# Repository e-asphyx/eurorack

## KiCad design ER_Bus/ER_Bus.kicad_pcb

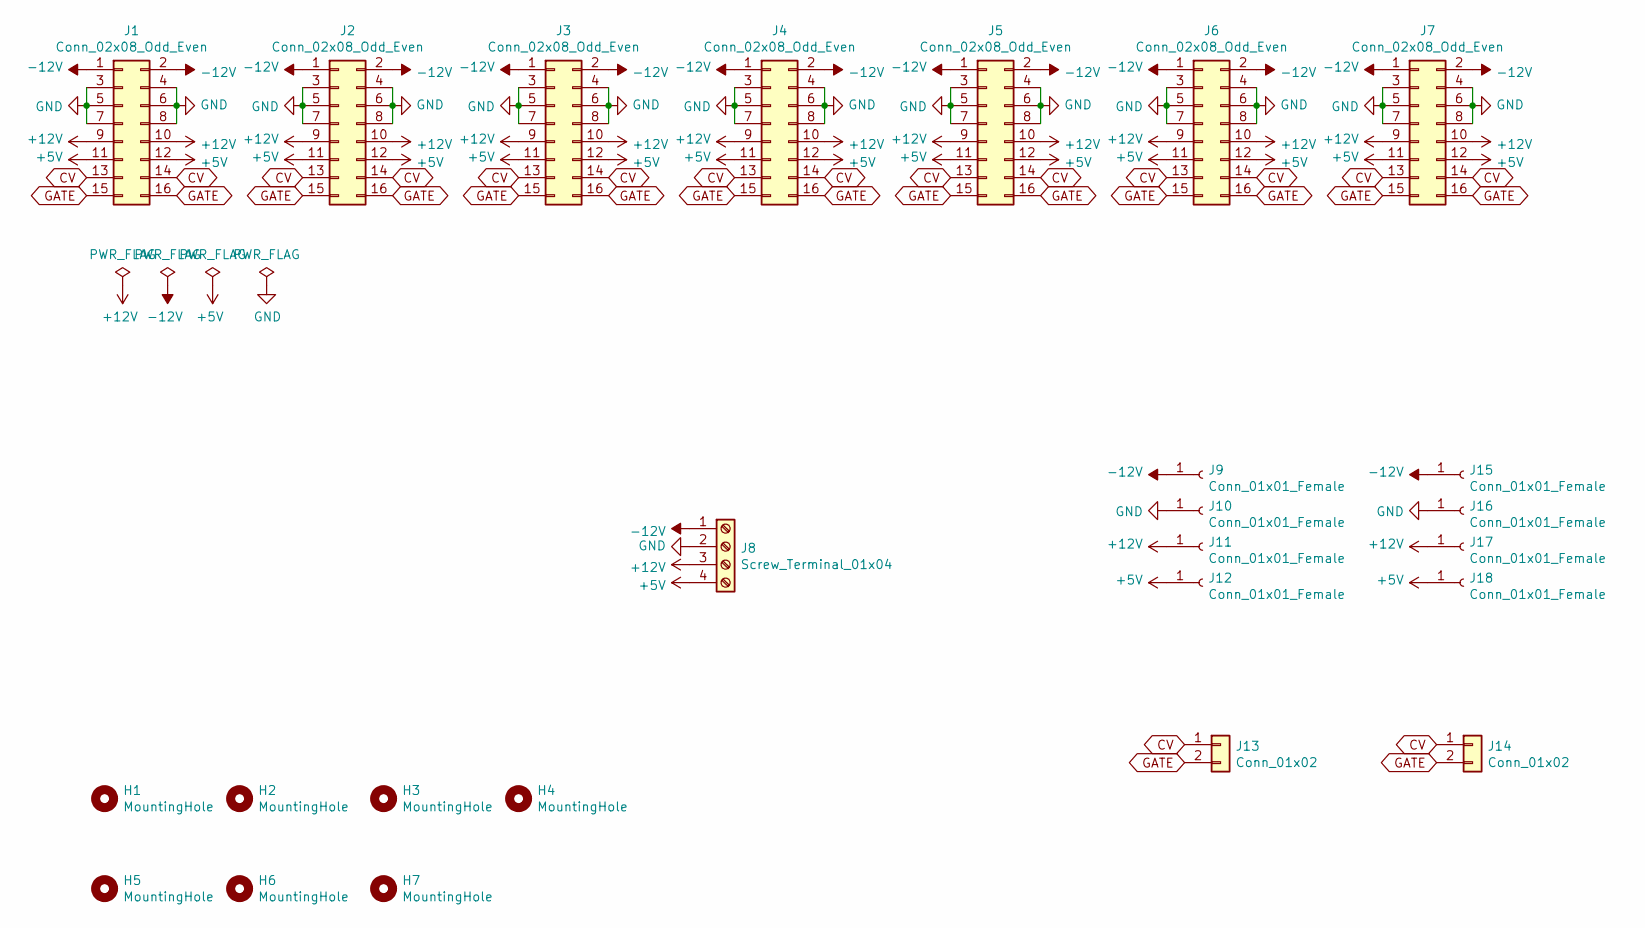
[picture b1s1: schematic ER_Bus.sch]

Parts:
H1, H2, H3, H4, H5, H6, H7: MountingHole; MountingHole_3.2mm_M3_Pad
J1, J2, J3, J4, J5, J6, J7: Conn_02x08_Odd_Even; IDC-Header_2x08_P2.54mm_Vertical
J8: Screw_Terminal_01x04; TerminalBlock_RND_205-00234_1x04_P5.08mm_Horizontal
J9, J10, J11, J12, J15, J16, J17, J18: Conn_01x01_Female; SolderWirePad_1x01_Drill1.5mm
J13, J14: Conn_01x02; JST_EH_B2B-EH-A_1x02_P2.50mm_Vertical

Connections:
+5V: J1.11, J1.12, J2.11, J2.12, J3.11, J3.12, J4.11, J4.12, J5.11, J5.12, J6.11, J6.12, J7.11, J7.12, J8.4, J12.1, J18.1
+12V: J1.9, J1.10, J2.9, J2.10, J3.9, J3.10, J4.9, J4.10, J5.9, J5.10, J6.9, J6.10, J7.9, J7.10, J8.3, J11.1, J17.1
-12V: J1.1, J1.2, J2.1, J2.2, J3.1, J3.2, J4.1, J4.2, J5.1, J5.2, J6.1, J6.2, J7.1, J7.2, J8.1, J9.1, J15.1
CV: J1.13, J1.14, J2.13, J2.14, J3.13, J3.14, J4.13, J4.14, J5.13, J5.14, J6.13, J6.14, J7.13, J7.14, J13.1, J14.1
GATE: J1.15, J1.16, J2.15, J2.16, J3.15, J3.16, J4.15, J4.16, J5.15, J5.16, J6.15, J6.16, J7.15, J7.16, J13.2, J14.2
GND: J1.3, J1.4, J1.5, J1.6, J1.7, J1.8, J2.3, J2.4, J2.5, J2.6, J2.7, J2.8, J3.3, J3.4, J3.5, J3.6, J3.7, J3.8, J4.3, J4.4, J4.5, J4.6, J4.7, J4.8, J5.3, J5.4, J5.5, J5.6, J5.7, J5.8, J6.3, J6.4, J6.5, J6.6, J6.7, J6.8, J7.3, J7.4, J7.5, J7.6, J7.7, J7.8, J8.2, J10.1, J16.1

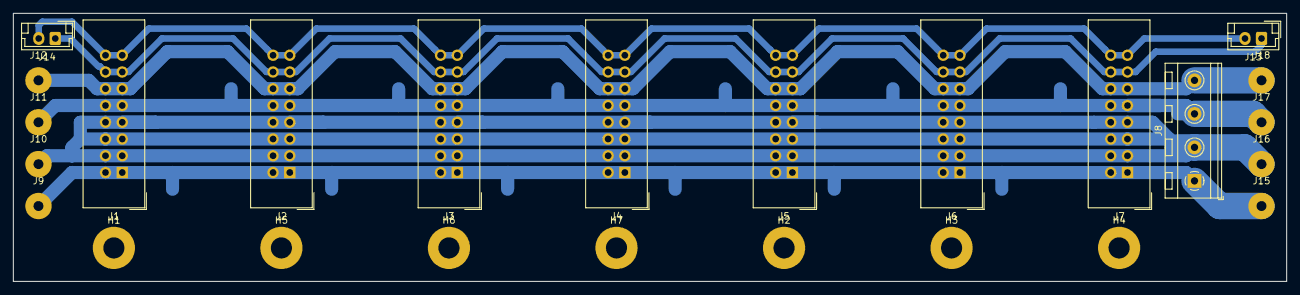
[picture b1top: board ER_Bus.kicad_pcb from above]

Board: 2 copper layers, 193.0 x 40.6 mm, 25 parts (0 on the bottom side), 6 nets.

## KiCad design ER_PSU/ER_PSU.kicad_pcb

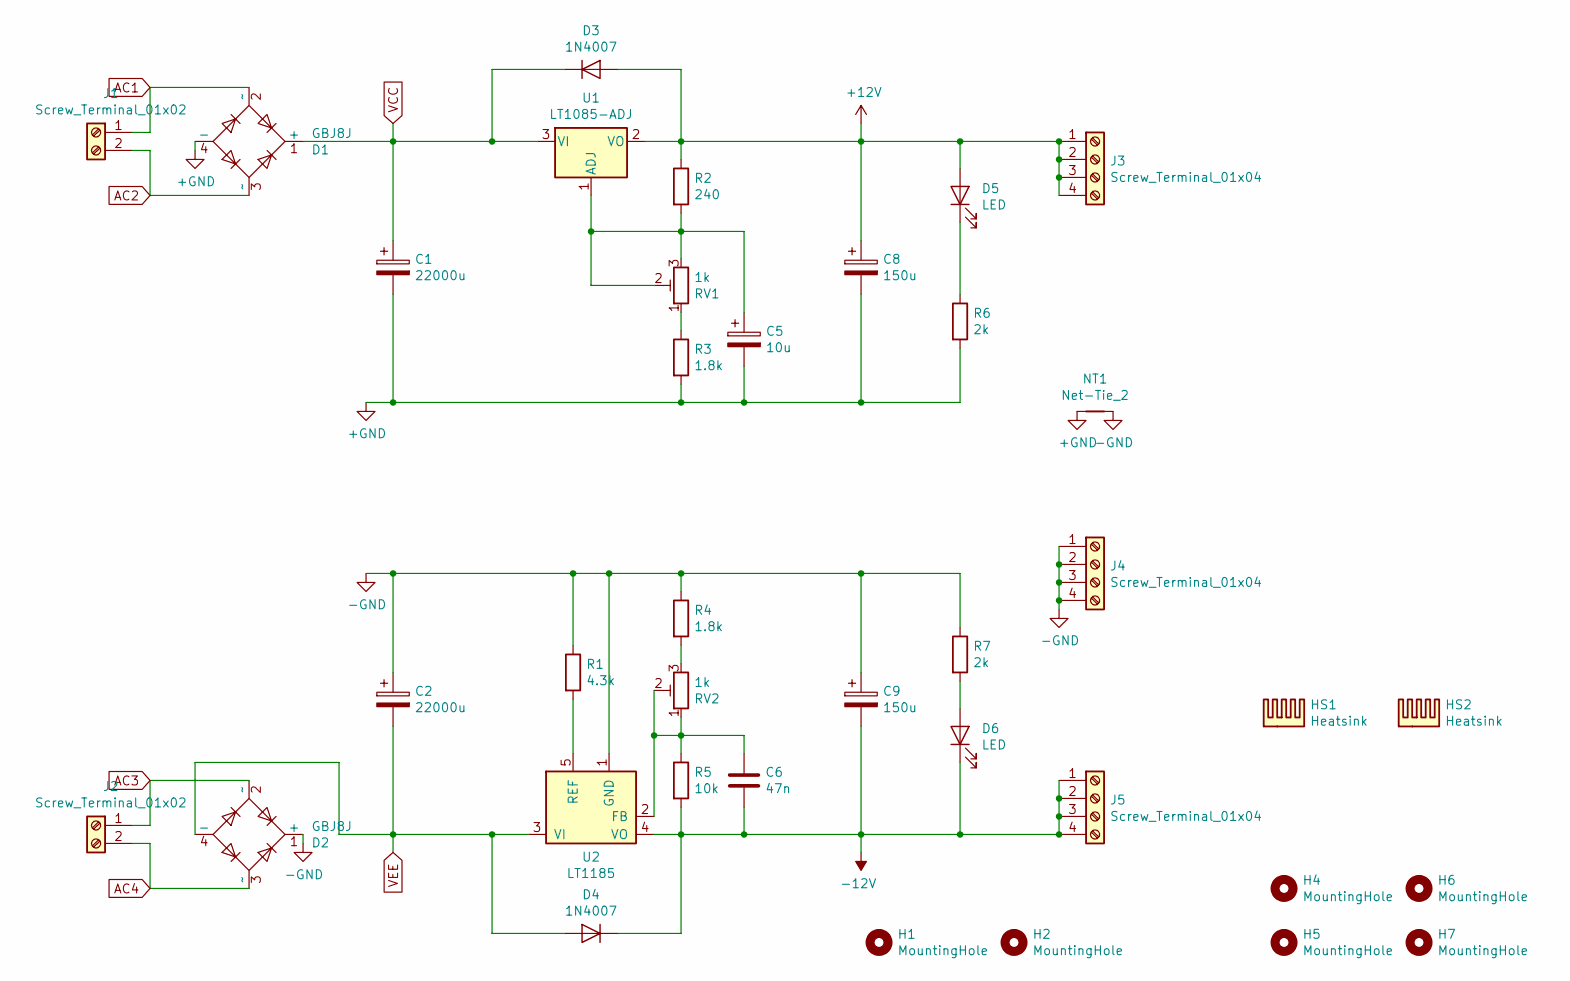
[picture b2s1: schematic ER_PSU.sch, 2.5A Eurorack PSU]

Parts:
C1, C2: 22000u; CP_Radial_D35.0mm_P10.00mm_SnapIn
C5: 10u; CP_Radial_D6.3mm_P2.50mm
C6: 47n; C_Rect_L13.0mm_W5.0mm_P10.00mm_FKS3_FKP3_MKS4
C8, C9: 150u; CP_Radial_D10.0mm_P5.00mm
D1, D2: GBJ8J; Diode_Bridge_25.0x4.6x15mm_P7.62mm
D3, D4: 1N4007; D_DO-41_SOD81_P12.70mm_Horizontal
D5, D6: LED; LED_D3.0mm
H1, H2, H4, H5, H6, H7: MountingHole; MountingHole_3.2mm_M3
HS1, HS2: Heatsink; Heatsink_Fischer_SK068_L75mm
J1, J2: Screw_Terminal_01x02; TerminalBlock_RND_205-00241_1x02_P10.16mm_Horizontal
J3, J4, J5: Screw_Terminal_01x04; TerminalBlock_RND_205-00234_1x04_P5.08mm_Horizontal
NT1: Net-Tie_2; NetTie-2_SMD_Pad12.7mm
R1: 4.3k; R_Axial_DIN0207_L6.3mm_D2.5mm_P10.16mm_Horizontal
R2: 240; R_Axial_DIN0207_L6.3mm_D2.5mm_P10.16mm_Horizontal
R3, R4: 1.8k; R_Axial_DIN0207_L6.3mm_D2.5mm_P10.16mm_Horizontal
R5: 10k; R_Axial_DIN0207_L6.3mm_D2.5mm_P10.16mm_Horizontal
R6, R7: 2k; R_Axial_DIN0207_L6.3mm_D2.5mm_P10.16mm_Horizontal
RV1, RV2: 1k; Potentiometer_Bourns_3296W_Vertical
U1: LT1085-ADJ; TO-220-3_Vertical
U2: LT1185; TO-220-5_P3.4x3.7mm_StaggerOdd_Lead3.8mm_Vertical

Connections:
+12V: C8.1, D3.2 (A), D5.2 (A), J3.1, J3.2, J3.3, J3.4, R2.1, U1.2 (VO)
+GND: C1.2, C5.2, C8.2, D1.4 (-), NT1.1, R3.2, R6.2
-12V: C6.2, C9.2, D4.1 (K), D6.1 (K), J5.1, J5.2, J5.3, J5.4, R5.2, U2.4 (VO)
-GND: C2.1, C9.1, D2.1 (+), J4.1, J4.2, J4.3, J4.4, NT1.2, R1.1, R4.1, R7.1, U2.1 (GND)
AC1: D1.2 (~~), J1.1
AC2: D1.3 (~~), J1.2
AC3: D2.2 (~~), J2.1
AC4: D2.3 (~~), J2.2
unnamed: C5.1, R2.2, RV1.2, RV1.3, U1.1 (ADJ)
unnamed: C6.1, R5.1, RV2.1, RV2.2, U2.2 (FB)
unnamed: D5.1 (K), R6.1
unnamed: D6.2 (A), R7.2
unnamed: R1.2, U2.5 (REF)
unnamed: R3.1, RV1.1
unnamed: R4.2, RV2.3
VCC: C1.1, D1.1 (+), D3.1 (K), U1.3 (VI)
VEE: C2.2, D2.4 (-), D4.2 (A), U2.3 (VI)

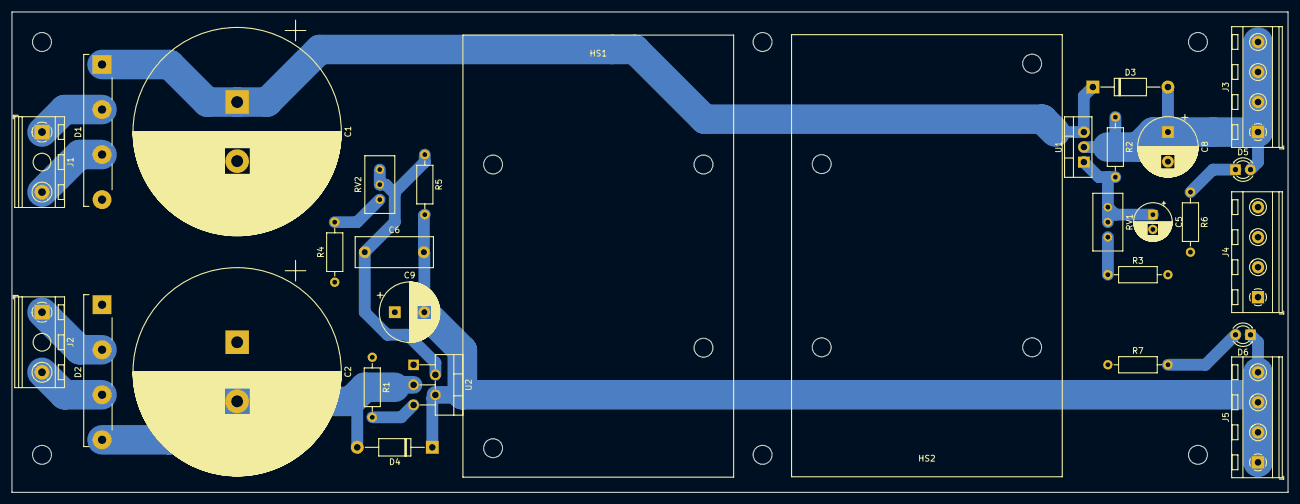
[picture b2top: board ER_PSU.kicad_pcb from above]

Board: 2 copper layers, 215.9 x 81.3 mm, 37 parts (1 on the bottom side), 17 nets.

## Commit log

2020-03-23 Eurorack PSU
2020-03-23 LTSpice PSU simulation
